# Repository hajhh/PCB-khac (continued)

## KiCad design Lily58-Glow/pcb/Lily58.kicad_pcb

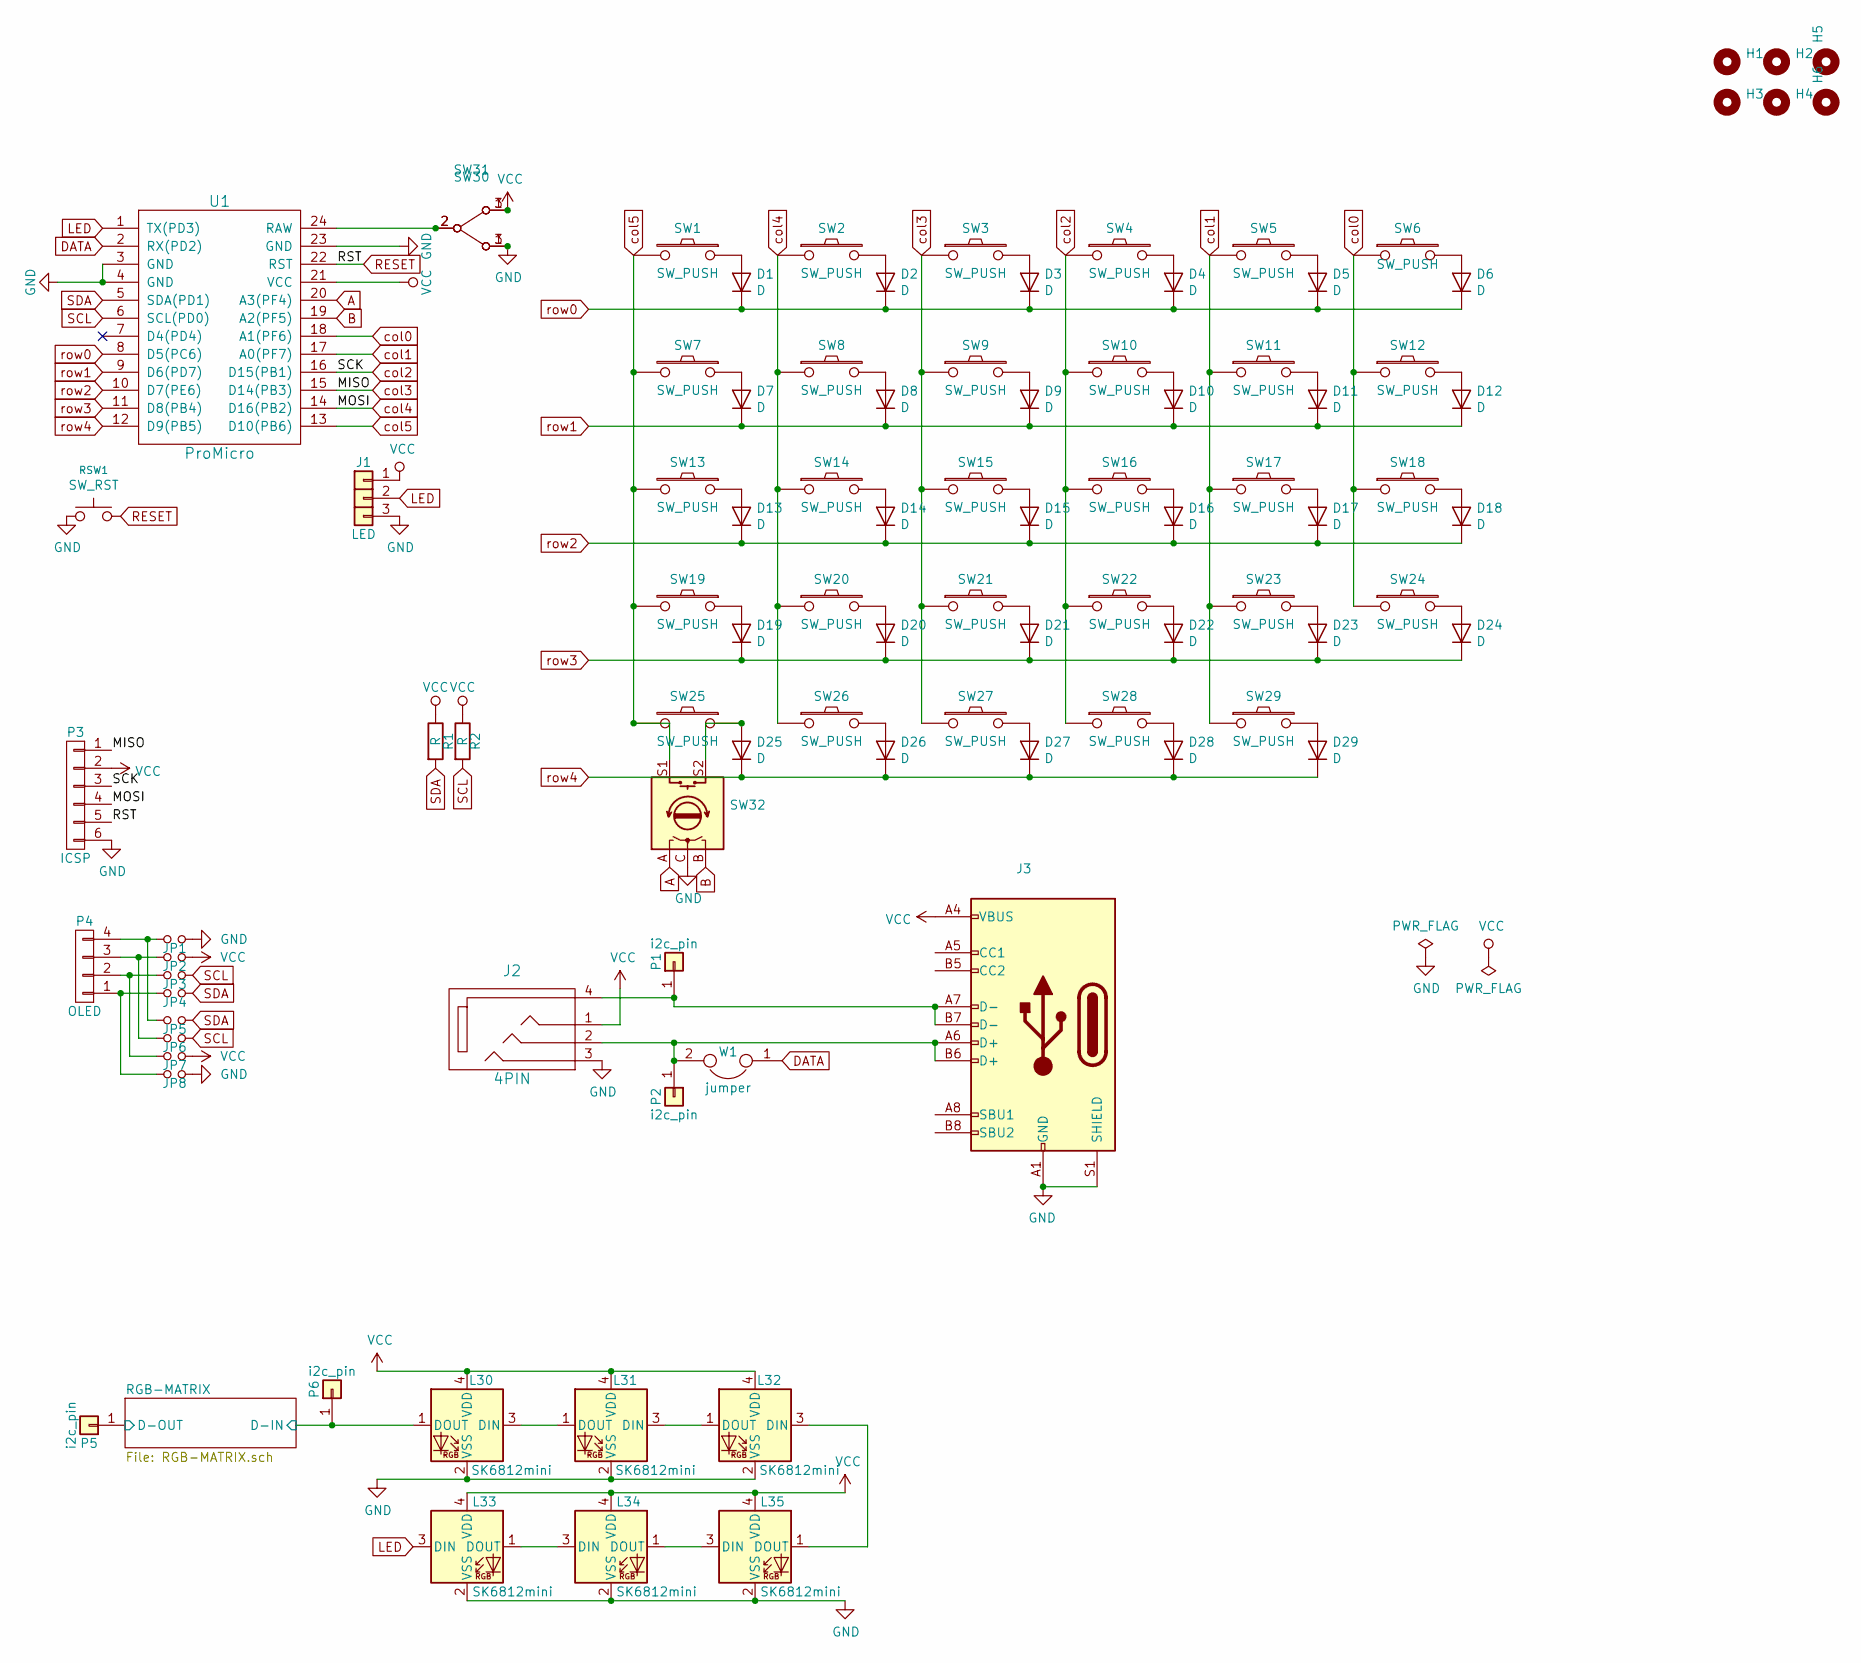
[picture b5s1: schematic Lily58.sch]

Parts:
D1, D2, D3, D4, D5, D6, D7, D8, D9, D10, D11, D12, D13, D14, D15, D16, D17, D18, D19, D20, D21, D22, D23, D24, D25, D26, D27, D28, D29: D; DIODE
H1, H2: MountingHole_2.2mm_M2_DIN965_Pad
H3, H6: lily58_logo_2
H4, H5: lily58_logo_1
J1: LED; StripLED
J2: 4PIN; MJ-4PP-9
J3: USB-C-16pin-hight
JP1, JP2, JP3, JP4, JP5, JP6, JP7, JP8: Jumper_NO_Small; Jumper
L30, L31, L32, L33, L34, L35: SK6812mini; SK6812MINI_underglow_rev
P1, P2, P5, P6: i2c_pin; 1pin_conn
P3: ICSP
P4: OLED; MY_SIL-4
R1, R2: R; RESISTOR_mini
RSW1: SW_RST; TACT_SWITCH_TVBP06
SW1, SW2, SW3, SW4, SW5, SW6, SW7, SW8, SW9, SW10, SW11, SW12, SW13, SW14, SW15, SW16, SW17, SW18, SW19, SW20, SW21, SW22, SW23, SW24, SW25, SW26, SW27, SW28, SW29: SW_PUSH; SW-1u-Aps-Split
SW30, SW31: SW_SPDT_PCM12
SW32: Econder
U1: ProMicro; ProMicro_rev2
W1: jumper; jumper_data

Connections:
/RGB-MATRIX/D-IN: L30.1 (DOUT), P6.1; also elsewhere on the board
/RGB-MATRIX/D-OUT: P5.1; also elsewhere on the board
A: SW32.A, U1.20 (A3(PF4))
B: SW32.B, U1.19 (A2(PF5))
DATA: U1.2 (RX(PD2)), W1.1
GND: J1.3, J2.3, J3.A1 (GND), J3.A12 (GND), J3.B1 (GND), J3.B12 (GND), J3.S1 (SHIELD), JP1.2, JP8.2, L30.2 (VSS), L31.2 (VSS), L32.2 (VSS), L33.2 (VSS), L34.2 (VSS), L35.2 (VSS), P3.6, RSW1.1, SW30.3 (C), SW31.1 (A), SW32.C, U1.3 (GND), U1.4 (GND), U1.23 (GND); also elsewhere on the board
LED: J1.2, L33.3 (DIN), U1.1 (TX(PD3))
unnamed: D1.2 (A), SW1.1
unnamed: D2.2 (A), SW2.2
unnamed: D3.2 (A), SW3.2
unnamed: D4.2 (A), SW4.2
unnamed: D5.2 (A), SW5.2
unnamed: D6.2 (A), SW6.2
unnamed: D7.2 (A), SW7.1
unnamed: D8.2 (A), SW8.2
unnamed: D9.2 (A), SW9.2
unnamed: D10.2 (A), SW10.2
unnamed: D11.2 (A), SW11.2
unnamed: D12.2 (A), SW12.2
unnamed: D13.2 (A), SW13.1
unnamed: D14.2 (A), SW14.2
unnamed: D15.2 (A), SW15.2
unnamed: D16.2 (A), SW16.2
unnamed: D17.2 (A), SW17.2
unnamed: D18.2 (A), SW18.2
unnamed: D19.2 (A), SW19.1
unnamed: D20.2 (A), SW20.2
unnamed: D21.2 (A), SW21.2
unnamed: D22.2 (A), SW22.2
unnamed: D23.2 (A), SW23.2
unnamed: D24.2 (A), SW24.2
unnamed: D25.2 (A), SW25.1, SW32.S2
unnamed: D26.2 (A), SW26.2
unnamed: D27.2 (A), SW27.2
unnamed: D28.2 (A), SW28.2
unnamed: D29.2 (A), SW29.2
unnamed: J2.2, J3.A6 (D+), J3.B6 (D+), P2.1, W1.2
unnamed: J2.4, J3.A7 (D-), J3.B7 (D-), P1.1
unnamed: JP1.1, JP5.1, P4.4
unnamed: JP2.1, JP6.1, P4.3
unnamed: JP3.1, JP7.1, P4.2
unnamed: JP4.1, JP8.1, P4.1
unnamed: L30.3 (DIN), L31.1 (DOUT)
unnamed: L31.3 (DIN), L32.1 (DOUT)
unnamed: L32.3 (DIN), L35.1 (DOUT)
unnamed: L33.1 (DOUT), L34.3 (DIN)
unnamed: L34.1 (DOUT), L35.3 (DIN)
unnamed: SW30.2 (B), SW31.2 (B), U1.24 (RAW)
RESET: P3.5, RSW1.2, U1.22 (RST)
SCL: JP3.2, JP6.2, R2.2, U1.6 (SCL(PD0))
SDA: JP4.2, JP5.2, R1.2, U1.5 (SDA(PD1))
VCC: J1.1, J2.1, J3.A4 (VBUS), J3.A9 (VBUS), J3.B4 (VBUS), J3.B9 (VBUS), JP2.2, JP7.2, L30.4 (VDD), L31.4 (VDD), L32.4 (VDD), L33.4 (VDD), L34.4 (VDD), L35.4 (VDD), P3.2, R1.1, R2.1, SW30.1 (A), SW31.3 (C), U1.21 (VCC); also elsewhere on the board
col0: SW6.1, SW12.1, SW18.1, SW24.1, U1.18 (A1(PF6))
col1: SW5.1, SW11.1, SW17.1, SW23.1, SW29.1, U1.17 (A0(PF7))
col2: P3.3, SW4.1, SW10.1, SW16.1, SW22.1, SW28.1, U1.16 (D15(PB1))
col3: P3.1, SW3.1, SW9.1, SW15.1, SW21.1, SW27.1, U1.15 (D14(PB3))
col4: P3.4, SW2.1, SW8.1, SW14.1, SW20.1, SW26.1, U1.14 (D16(PB2))
col5: SW1.2, SW7.2, SW13.2, SW19.2, SW25.2, SW32.S1, U1.13 (D10(PB6))
row0: D1.1 (K), D2.1 (K), D3.1 (K), D4.1 (K), D5.1 (K), D6.1 (K), U1.8 (D5(PC6))
row1: D7.1 (K), D8.1 (K), D9.1 (K), D10.1 (K), D11.1 (K), D12.1 (K), U1.9 (D6(PD7))
row2: D13.1 (K), D14.1 (K), D15.1 (K), D16.1 (K), D17.1 (K), D18.1 (K), U1.10 (D7(PE6))
row3: D19.1 (K), D20.1 (K), D21.1 (K), D22.1 (K), D23.1 (K), D24.1 (K), U1.11 (D8(PB4))
row4: D25.1 (K), D26.1 (K), D27.1 (K), D28.1 (K), D29.1 (K), U1.12 (D9(PB5))

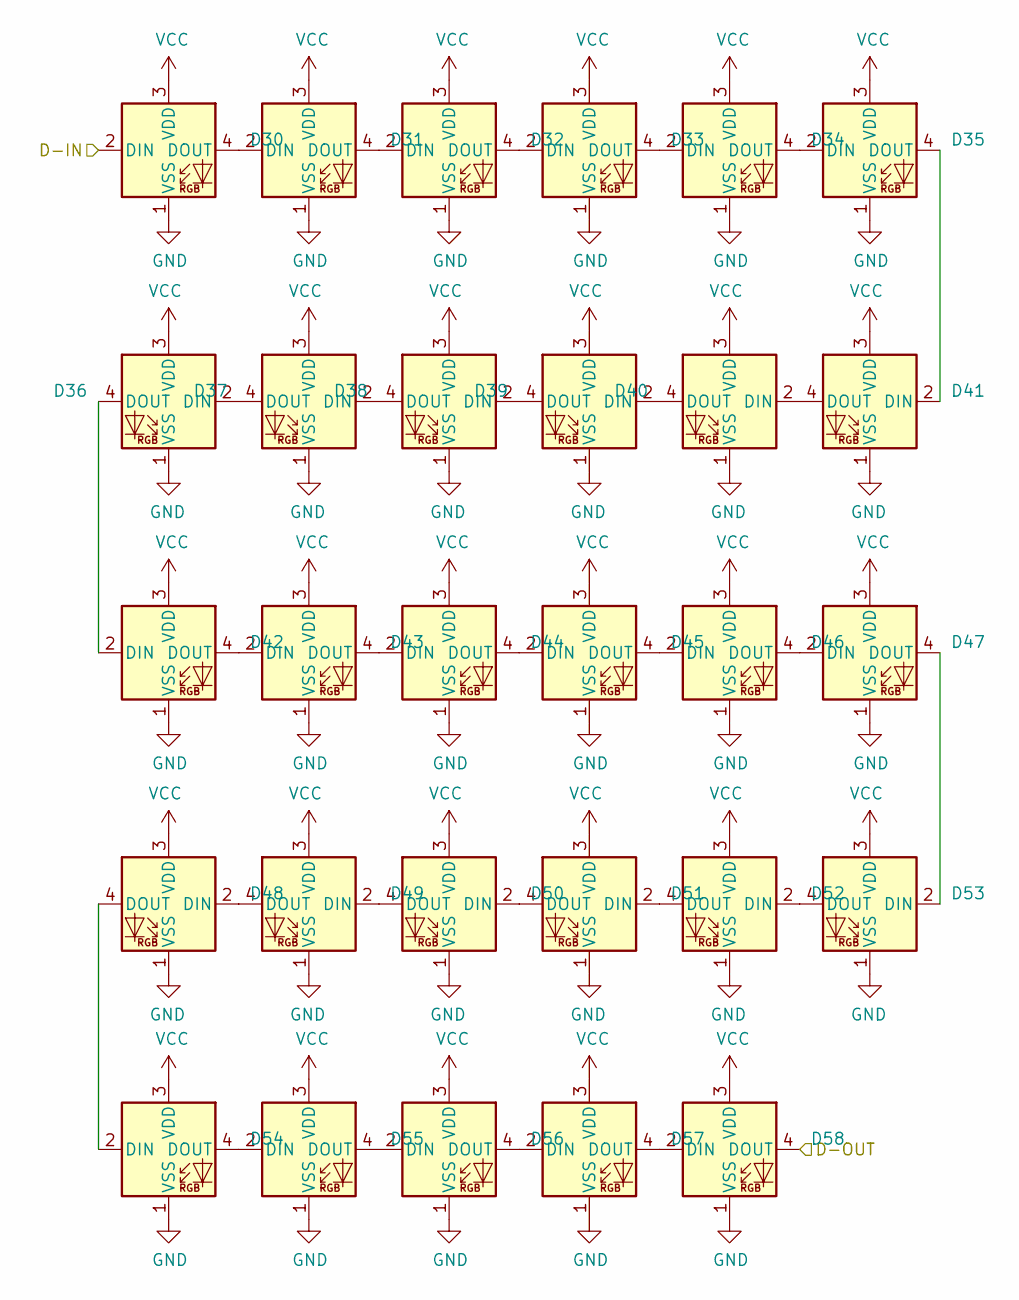
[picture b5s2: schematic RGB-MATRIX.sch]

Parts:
D30, D31, D32, D33, D34, D35, D42, D43, D44, D45, D46, D47, D55, D56, D57, D58: SK6812MINI-E
D36, D37, D38, D39, D40, D41, D48, D49, D50, D51, D52, D53, D54: SK6812MINI-E-R2L

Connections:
/RGB-MATRIX/D-IN: D30.2 (DIN); also elsewhere on the board
/RGB-MATRIX/D-OUT: D58.4 (DOUT); also elsewhere on the board
GND: D30.1 (VSS), D31.1 (VSS), D32.1 (VSS), D33.1 (VSS), D34.1 (VSS), D35.1 (VSS), D36.1 (VSS), D37.1 (VSS), D38.1 (VSS), D39.1 (VSS), D40.1 (VSS), D41.1 (VSS), D42.1 (VSS), D43.1 (VSS), D44.1 (VSS), D45.1 (VSS), D46.1 (VSS), D47.1 (VSS), D48.1 (VSS), D49.1 (VSS), D50.1 (VSS), D51.1 (VSS), D52.1 (VSS), D53.1 (VSS), D54.1 (VSS), D55.1 (VSS), D56.1 (VSS), D57.1 (VSS), D58.1 (VSS); also elsewhere on the board
unnamed: D30.4 (DOUT), D31.2 (DIN)
unnamed: D31.4 (DOUT), D32.2 (DIN)
unnamed: D32.4 (DOUT), D33.2 (DIN)
unnamed: D33.4 (DOUT), D34.2 (DIN)
unnamed: D34.4 (DOUT), D35.2 (DIN)
unnamed: D35.4 (DOUT), D41.2 (DIN)
unnamed: D36.2 (DIN), D37.4 (DOUT)
unnamed: D36.4 (DOUT), D42.2 (DIN)
unnamed: D37.2 (DIN), D38.4 (DOUT)
unnamed: D38.2 (DIN), D39.4 (DOUT)
unnamed: D39.2 (DIN), D40.4 (DOUT)
unnamed: D40.2 (DIN), D41.4 (DOUT)
unnamed: D42.4 (DOUT), D43.2 (DIN)
unnamed: D43.4 (DOUT), D44.2 (DIN)
unnamed: D44.4 (DOUT), D45.2 (DIN)
unnamed: D45.4 (DOUT), D46.2 (DIN)
unnamed: D46.4 (DOUT), D47.2 (DIN)
unnamed: D47.4 (DOUT), D53.2 (DIN)
unnamed: D48.2 (DIN), D49.4 (DOUT)
unnamed: D48.4 (DOUT), D54.2 (DIN)
unnamed: D49.2 (DIN), D50.4 (DOUT)
unnamed: D50.2 (DIN), D51.4 (DOUT)
unnamed: D51.2 (DIN), D52.4 (DOUT)
unnamed: D52.2 (DIN), D53.4 (DOUT)
unnamed: D54.4 (DOUT), D55.2 (DIN)
unnamed: D55.4 (DOUT), D56.2 (DIN)
unnamed: D56.4 (DOUT), D57.2 (DIN)
unnamed: D57.4 (DOUT), D58.2 (DIN)
VCC: D30.3 (VDD), D31.3 (VDD), D32.3 (VDD), D33.3 (VDD), D34.3 (VDD), D35.3 (VDD), D36.3 (VDD), D37.3 (VDD), D38.3 (VDD), D39.3 (VDD), D40.3 (VDD), D41.3 (VDD), D42.3 (VDD), D43.3 (VDD), D44.3 (VDD), D45.3 (VDD), D46.3 (VDD), D47.3 (VDD), D48.3 (VDD), D49.3 (VDD), D50.3 (VDD), D51.3 (VDD), D52.3 (VDD), D53.3 (VDD), D54.3 (VDD), D55.3 (VDD), D56.3 (VDD), D57.3 (VDD), D58.3 (VDD); also elsewhere on the board

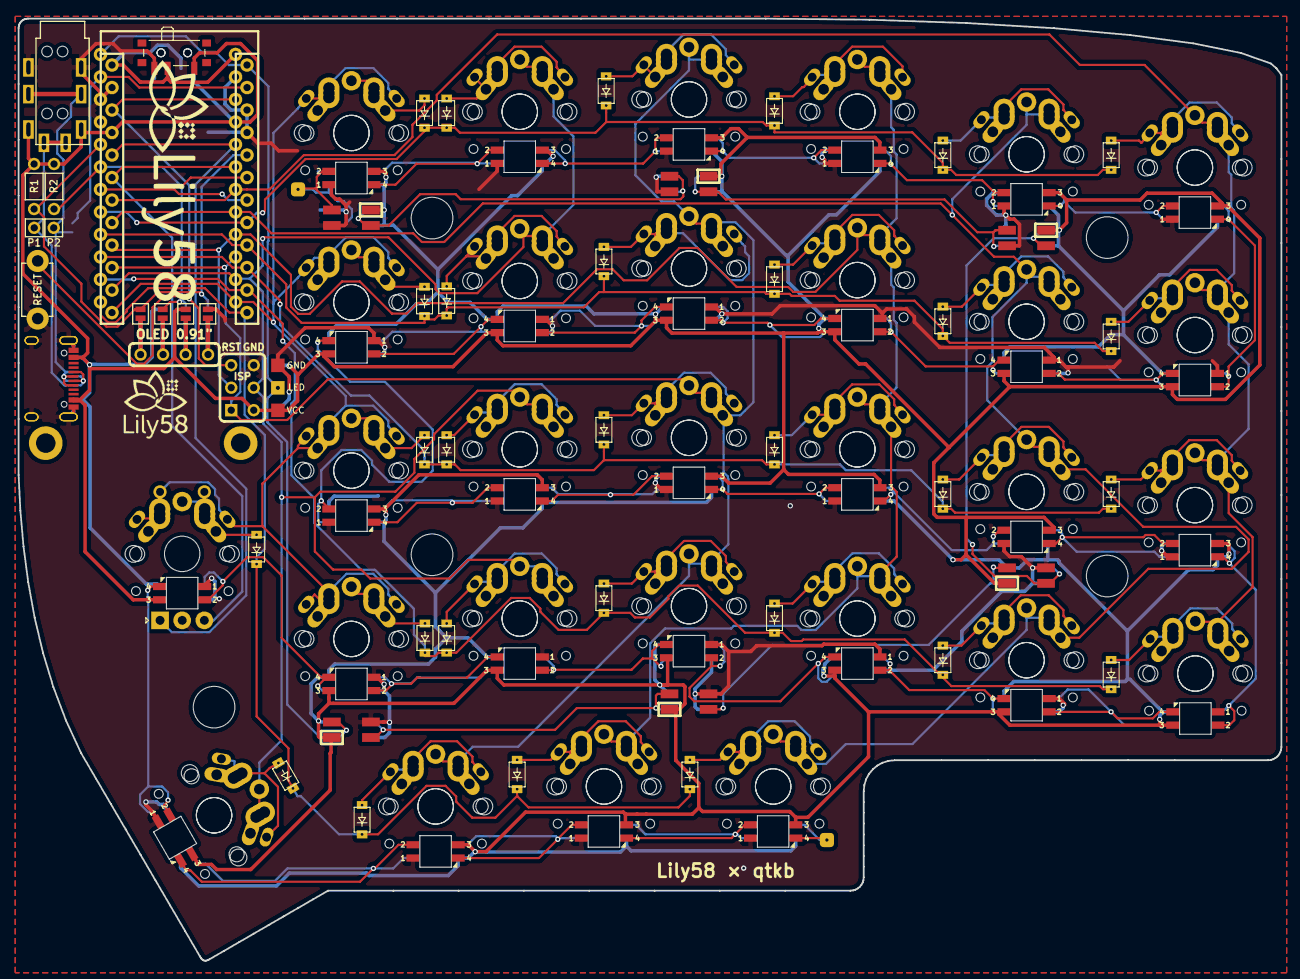
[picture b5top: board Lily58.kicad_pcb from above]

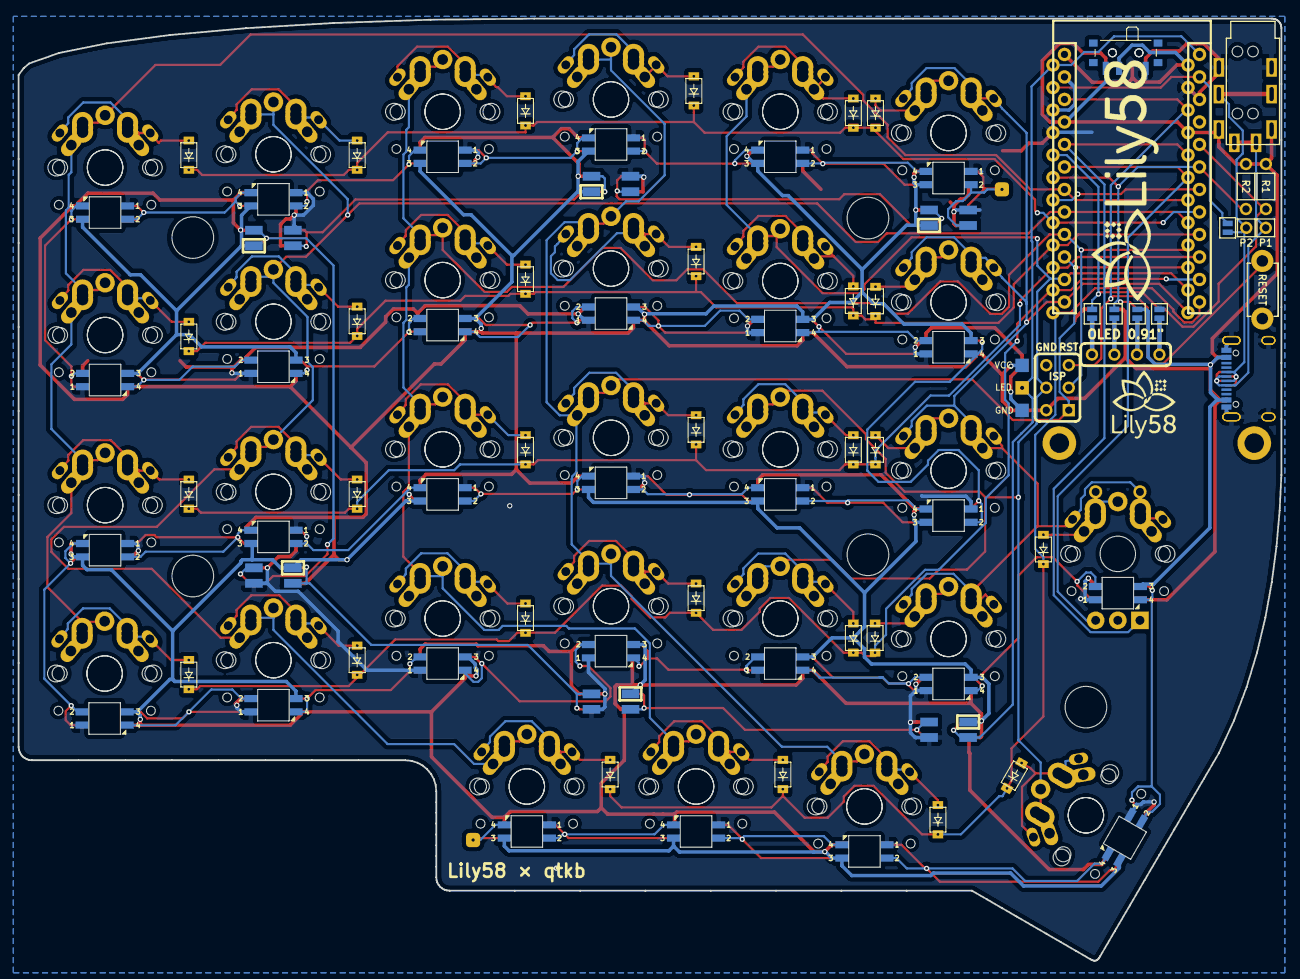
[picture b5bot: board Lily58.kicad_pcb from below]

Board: 2 copper layers, 142.5 x 106.3 mm, 124 parts (37 on the bottom side), 91 nets.
